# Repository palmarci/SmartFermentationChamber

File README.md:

# Smart Fermentation Chamber

This is a SW + HW (and woodworking) project to create an insulated chamber with regulated temperature and humidity to perform food fermentation. This project is currently work-in-progress, please adapt the design for your needs and also make sure to double check the schematic/PCB before ordering.

## Table of contents
- [Table of contents](#table-of-contents)
- [Architecture](#architecture)
- [Firmware](#firmware)
- [PCB](#pcb)
- [Bill of materials](#bill-of-materials)
  - [Main components](#main-components)
  - [PCB parts](#pcb-parts)
- [Pictures](#pictures)
  - [Box](#box)
  - [Web server graphs](#web-server-graphs)
  - [ESP Web UI](#esp-web-ui)
- [TODOs](#todos)

## Architecture

The ESP32 gathers environmental data through sensors, evaluates it against target values, and manages the heater and humidifiers accordingly. This data is logged to a Python controller via MQTT, which generates graphs viewable through a web server. The ESP32 is configurable via a built-in web interface powered by [ESPUI](https://github.com/s00500/ESPUI). Additionally, the controller can send real-time alerts to a smartphone using the Telegram API. An optional 230V dimmer is available to regulate the heater's current based on the size of the heated space (setting is done via a potentiometer externally to the whole control circuit).

<picture>
    <source srcset="doc/architecture_dark.png"  media="(prefers-color-scheme: dark)">
    
</picture>

## Firmware

It is a PlatformIO project. There is a [bug](https://github.com/lorol/LITTLEFS/pull/56
) in the external littlefs library, I had to fix it manually to get the FW compiling. The [fix](https://github.com/lorol/LITTLEFS/issues/43#issuecomment-1763347319
) is very easy to do.

## PCB

This is my first-ever PCB design, created in KiCad and manufactured by JLCPCB. Most of the routing was done using the auto-router, so please go easy on me. I made some mistakes, most notably I used an incorrect ESP devboard, these were fixed in 2.2, however I have not ordered those.

## Bill of materials

Prices are for one working unit with shipping, the date of prices is 2025.01. 
I ordered my parts from [Hestore](http://hestore.hu), if anyone needs to look up part numbers.

### Main components
|Name  |Link|Price |Description         |
|----------|-----|----|----------|
|*220V 300W Incubator heater Insulation-Thermostatic PTC ceramic air heater* | https://www.aliexpress.com/item/1005007503406690.html | 12 euro | You should buy one with a fan, I added one externally!<br> |
|*DC 5V Switchable Four Spray Humidifier Module Atomization Control Board DIY Ultrasonic Atomizer* | https://www.aliexpress.com/item/1005007493271175.html | 6 euro | Make sure to order one without a button, which powers on right after voltage is present<br>|
| NodeMCU ESP-32S development board | https://www.aliexpress.com/w/wholesale-nodemcu-32s.html | 6 euro | - | 
| PCB parts | - | 17 euro | *see BOM below* |
| PCB itself | https://jlcpcb.com/ | 22 euro *(for minimum order of 5 boards)* | I am not providing Gerber files, you will have to check the board/modify it if you need something, and just create the ZIP for yourself in KiCad!
| Wood + insulation | your local hardware store | max 20 euro | I don't remember the exact price
| *2000/4000W High Power Thyristor Electronic Voltage AC 220V Regulator Dimming Speed Temperature Regulation control switch* | https://www.aliexpress.com/item/1005006015316145.html | 5 euro |  |
| BME280 sensor | https://www.aliexpress.com/w/wholesale-bme280-sensor.html | 4 euro |  |
| Waterproof DS18B20 Temperature Sensor | https://www.aliexpress.com/item/1005001601986600.html | 4 euro | |
| **Total** | - | **~100 euro** | + cables, wires and misc soldering stuff |

### PCB parts

|Quantity  |Item name|Description         |
|----------|---------|--------------------|
|6         |1000 uF / 35V|Capacitor 12.5mm/5mm       |
|5         |LED 5 mm D-RD|LED                 |
|1         |1N4007   |Diode               |
|1|	? |4.7k Resistor            |
|3|	? |220R Resistor            |
|2|	?| 10k Resistor            |
|1|	? |1.5k Resistor            |
|2|	?|500R Resistor            |
|1         |?   |NPN transistor      |
|1         |BAT85    |Schottky-diode      |
|3         |ZL262-20SG|Pin header          |
|1         |IRLZ44NPBF|FET N               |
|1         |SRD-5VDC-SL-C|Relay, SPDT, 5V DC, 10A / 250V AC|
|1         |330uH / 1.2A / 630mR|Inductor            |
|1         |PTF/78   |Fuse holder, socket, 5x20mm|
|1         |BS232    |Fuse holder cover   |
|3         | ? |PCB terminal block, 90 degrees, 0.5cm, 2-pole|
|1         | ? |PCB terminal block, 90 degrees, 0.5cm, 4-pole|
|3         | ?|PCB terminal block, 90 degrees, 0.5cm, 3-pole|
|1         |XL2576S-5.0E1|Voltage stabilizer IC, both TO220 and TO263 fit |
|3         |5X20-F-3A|Fuse, fusible, glass, fast, 5x20mm, 250V AC, 3A|

## Pictures

### Box

### Web server graphs
<br>
<br>

### ESP Web UI
<br>
<br>

## TODOs
- went hole with a steppermotor  
- hum & temp updating at the same time bug

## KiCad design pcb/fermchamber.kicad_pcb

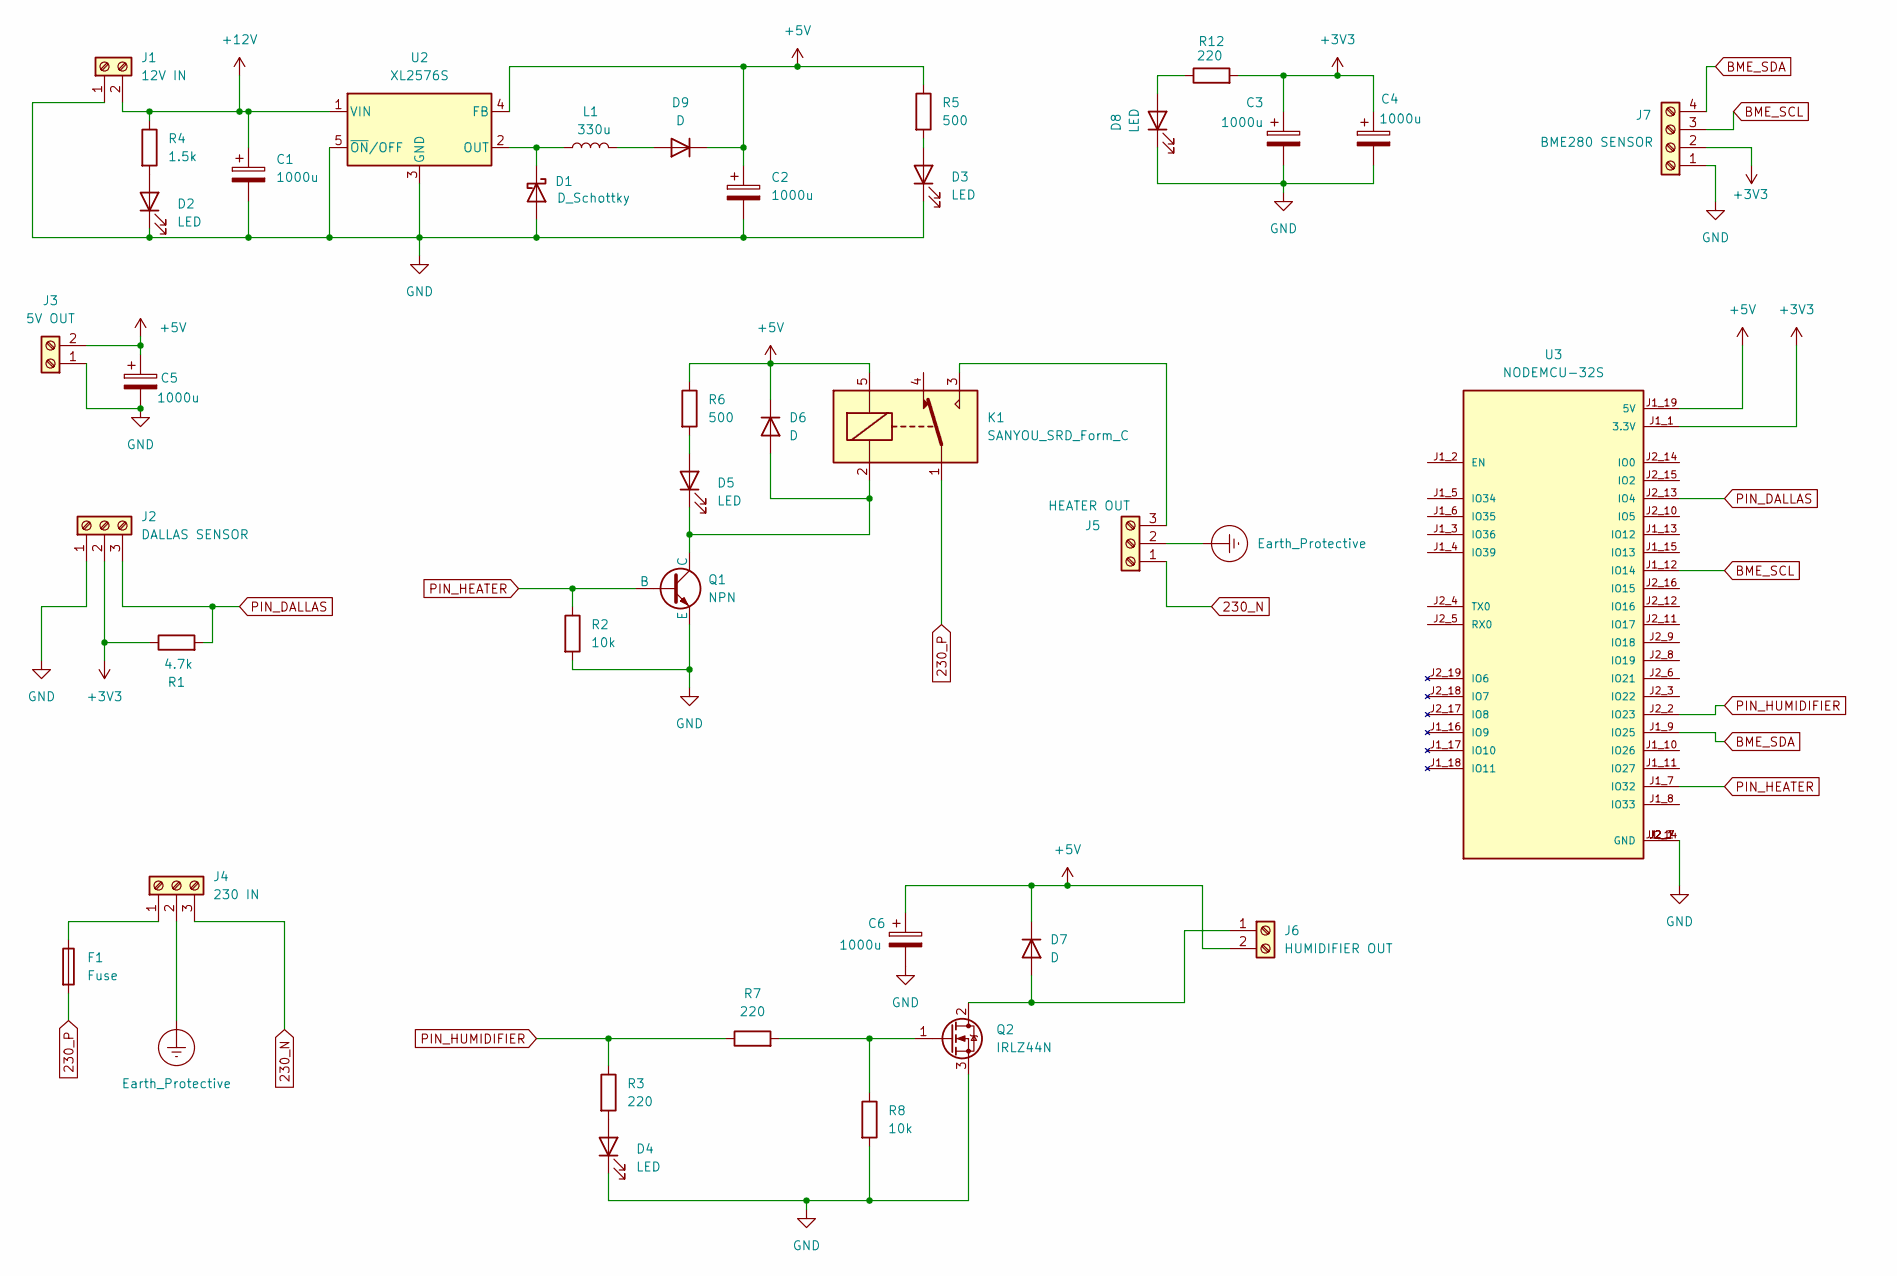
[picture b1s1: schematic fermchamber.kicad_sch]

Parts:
C1, C2, C3, C4, C5, C6: 1000u; CP_Radial_D12.5mm_P5.00mm
D1: D_Schottky; D_A-405_P7.62mm_Horizontal
D2, D3, D4, D5, D8: LED; LED_D3.0mm
D6, D7, D9: D; D_A-405_P7.62mm_Horizontal
F1: Fuse; Fuseholder_Cylinder-5x20mm_Schurter_0031_8201_Horizontal_Op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
J1: 12V IN; TerminalBlock_Phoenix_MKDS-1,5-2-5.08_1x02_P5.08mm_Horizont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
J2: DALLAS SENSOR; TerminalBlock_Phoenix_MKDS-1,5-3-5.08_1x03_P5.08mm_Horizont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
J3: 5V OUT; TerminalBlock_Phoenix_MKDS-1,5-2-5.08_1x02_P5.08mm_Horizont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
J4: 230 IN; TerminalBlock_Phoenix_MKDS-1,5-3-5.08_1x03_P5.08mm_Horizont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
J5: HEATER OUT; TerminalBlock_Phoenix_MKDS-1,5-3-5.08_1x03_P5.08mm_Horizont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
J6: HUMIDIFIER OUT; TerminalBlock_Phoenix_MKDS-1,5-2-5.08_1x02_P5.08mm_Horizont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
J7: BME280 SENSOR; TerminalBlock_Phoenix_MKDS-1,5-4_1x04_P5.00mm_Horizontal
K1: SANYOU_SRD_Form_C; Relay_SPDT_SANYOU_SRD_Series_Form_C
L1: 330u; L_Radial_D10.0mm_P5.00mm_Fastron_07P
Q1: NPN; TO-126-3_Vertical
Q2: IRLZ44N; TO-220-3_Vertical
R1: 4.7k; R_Axial_DIN0411_L9.9mm_D3.6mm_P12.70mm_Horizontal
R2, R8: 10k; R_Axial_DIN0411_L9.9mm_D3.6mm_P12.70mm_Horizontal
R3, R7, R12: 220; R_Axial_DIN0411_L9.9mm_D3.6mm_P12.70mm_Horizontal
R4: 1.5k; R_Axial_DIN0411_L9.9mm_D3.6mm_P12.70mm_Horizontal
R5, R6: 500; R_Axial_DIN0411_L9.9mm_D3.6mm_P12.70mm_Horizontal
U2: XL2576S; TO-220-5_Vertical
U3: NODEMCU-32S; MODULE_NODEMCU-32S; PARTREV V1

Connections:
230_N: J4.3, J5.1
230_P: F1.2, K1.1
+3V3: C3.1, C4.1, J2.2, J7.2, R1.1, R12.2, U3.J1_1 (3.3V)
+5V: C2.1, C5.1, C6.1, D6.1 (K), D7.1 (K), D9.1 (K), J3.2, J6.2, K1.5, R5.1, R6.1, U2.4 (FB), U3.J1_19 (5V)
+12V: C1.1, J1.2, R4.1, U2.1 (VIN)
BME_SCL: J7.3, U3.J1_12 (IO14)
BME_SDA: J7.4, U3.J1_9 (IO25)
Earth_Protective: J4.2, J5.2
GND: C1.2, C2.2, C3.2, C4.2, C5.2, C6.2, D1.2 (A), D2.1 (K), D3.1 (K), D4.1 (K), D8.1 (K), J1.1, J2.1, J3.1, J7.1, Q1.3 (E), Q2.3 (S), R2.2, R8.2, U2.3 (GND), U2.5 (~ON/OFF), U3.J1_14 (GND), U3.J2_1 (GND), U3.J2_7 (GND)
unnamed: D1.1 (K), L1.1, U2.2 (OUT)
unnamed: D2.2 (A), R4.2
unnamed: D3.2 (A), R5.2
unnamed: D4.2 (A), R3.2
unnamed: D5.2 (A), R6.2
unnamed: D5.1 (K), D6.2 (A), K1.2, Q1.1 (C)
unnamed: D7.2 (A), J6.1, Q2.2 (D)
unnamed: D8.2 (A), R12.1
unnamed: D9.2 (A), L1.2
unnamed: F1.1, J4.1
unnamed: J5.3, K1.3
unnamed: Q2.1 (G), R7.2, R8.1
PIN_DALLAS: J2.3, R1.2, U3.J2_13 (IO4)
PIN_HEATER: Q1.2 (B), R2.1, U3.J1_7 (IO32)
PIN_HUMIDIFIER: R3.1, R7.1, U3.J2_2 (IO23)

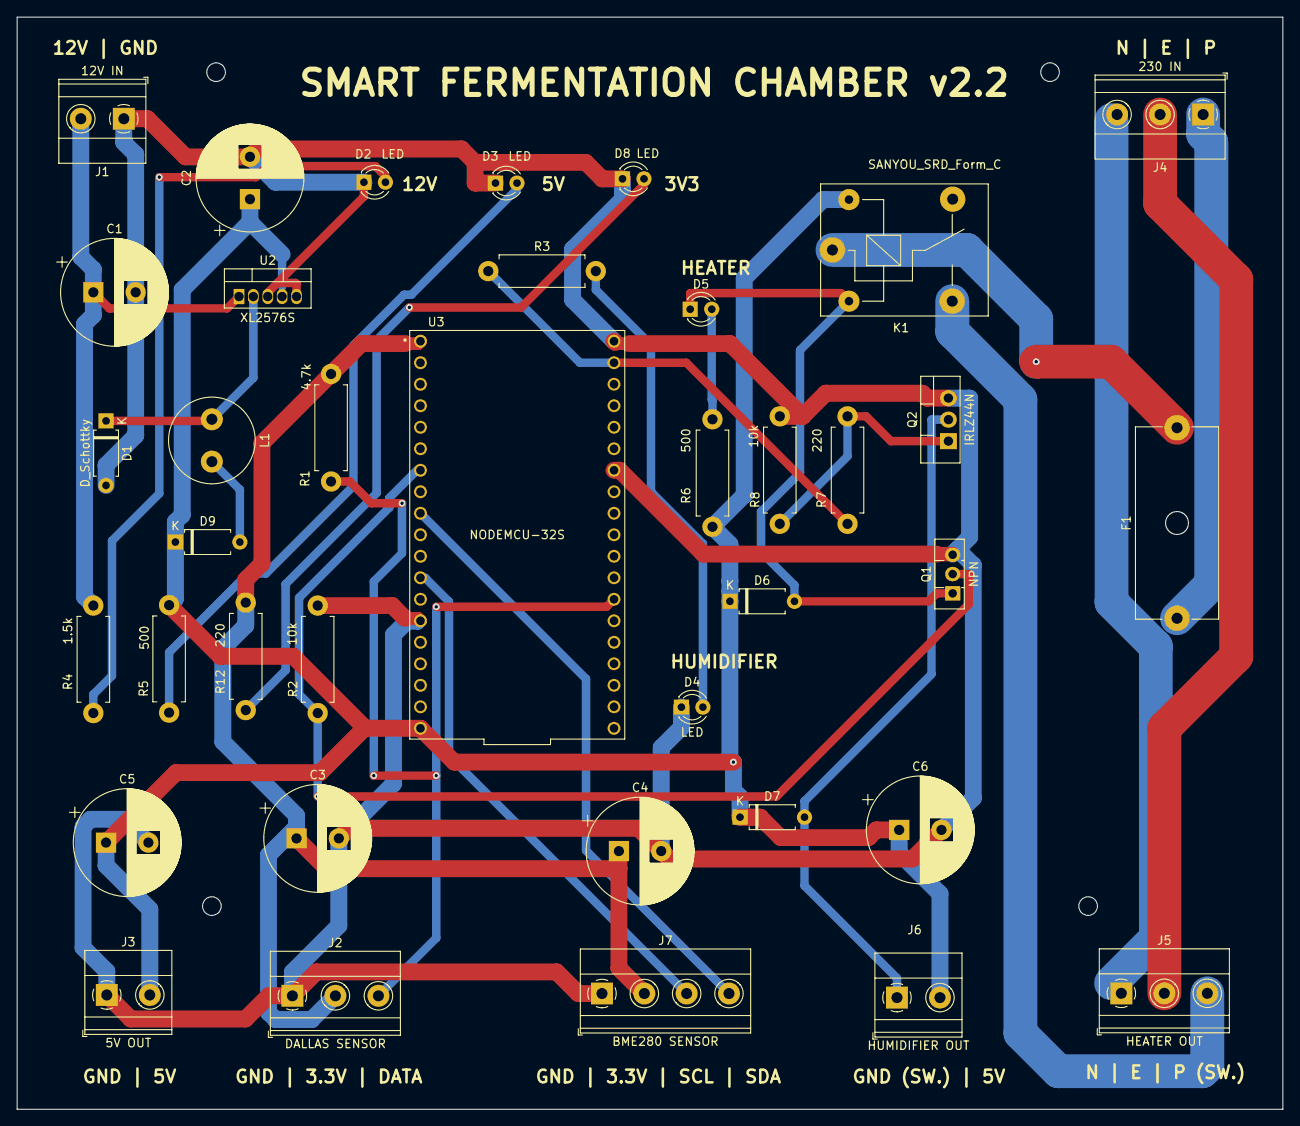
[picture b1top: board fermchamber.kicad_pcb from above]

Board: 2 copper layers, 149.5 x 129.0 mm, 38 parts (0 on the bottom side), 24 nets.

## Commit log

2024-03-12 adding files
2024-03-12 refactoring code
2024-03-12 refactor
2024-03-12 first buildable & refactored codebase
2024-03-12 first running build on the chip
2024-03-12 adding todos, small fix in web update logic
2024-03-13 adding placeholder control script; added auto restart task; added ability to kill running tasks; added invalid sensor reading last value feature;
2024-03-13 added every settings to nvm saving logic; added version into webui, updated ordering, fixed textbox enter problem
2024-03-13 fixed build errors; formatted code
2024-03-13 added buffering for web ui inputs; added startup alive checks for sensors; fixed nvm storing for every setting; added comments & info texts
2024-03-13 updating every web ui element on main window; increasing stack size for tasks
2024-03-15 implementing control.py; adding macros & debug settings into config.h; fixing bugs
2024-03-15 moving task delays to beginning, adding gpio insertion option, fixing timer logic in control script
2024-03-15 removing wifi credentials, ooops
2024-03-15 creating seperate file for wifi secrets
2024-03-15 adding secret to gitignore
2024-03-15 not tracking secret.h anymore
2024-03-15 returning to old config format
2024-03-17 reworked autopilot enable logic, added readme
2024-03-17 implemented graph generation in control script, fixed autopilot firing logic, fixed library defs in platformio config
2024-03-22 moves tasks from main, added helper task and option to control the humidifer via an extra transistor
2025-01-02 adding rewritten controller, new folder structure, adding secrets files for non tracking credentials
2025-01-02 adding secrets to gitignore
2025-01-02 stop tracking secrets files
2025-01-02 adding pcb files and gitignore from kicad
2025-01-02 updating readme, adding all documentation, making the repo public
2025-01-02 adding pictures and wording in readme
2025-01-02 adding TODOs
2025-01-02 adding TODOs in readme
2025-01-08 fixed capactior, inductor and, voltage ic footprint in schematic; added missing labels on the pcb; clarified and added missing items in the BOM
2025-01-12 renaming pins, adding sensor offsetting in config, adding TODOs
2025-01-12 fixing TODOs in documentation
2025-01-12 changed esp board to nodemcu 32s, limited current on leds, added diode for 5v usb programming backfeed, made switched labels more clear, fixed dallas data bus pull up, added pcb holes for mounting, r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
2025-02-16 rewrote controller; bugfix in wifi communication; bugfix in nvm target handling
2025-02-16 moved flask to background thread
2025-02-16 adding TODO for bug
2025-02-18 adding experimental pid support; switching to absolute humidity targetting; adding relay protection feature; made wifi more stable; fixed reboot crash problem; small changes in controller; cleaned an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
2025-02-18 fixing graph timestamps
2025-02-19 adding duty cycle measurement and graph generation; removed unnecessary pid test; implemented force heater mode;
2025-02-19 adding gitignore
2025-02-19 adding new pictures and updating readme
2025-02-19 changing image sizes because of web
2025-02-22 adding experimental (not working) ota and prediction support; renaming controller to web gui
2025-04-20 adding todos'
